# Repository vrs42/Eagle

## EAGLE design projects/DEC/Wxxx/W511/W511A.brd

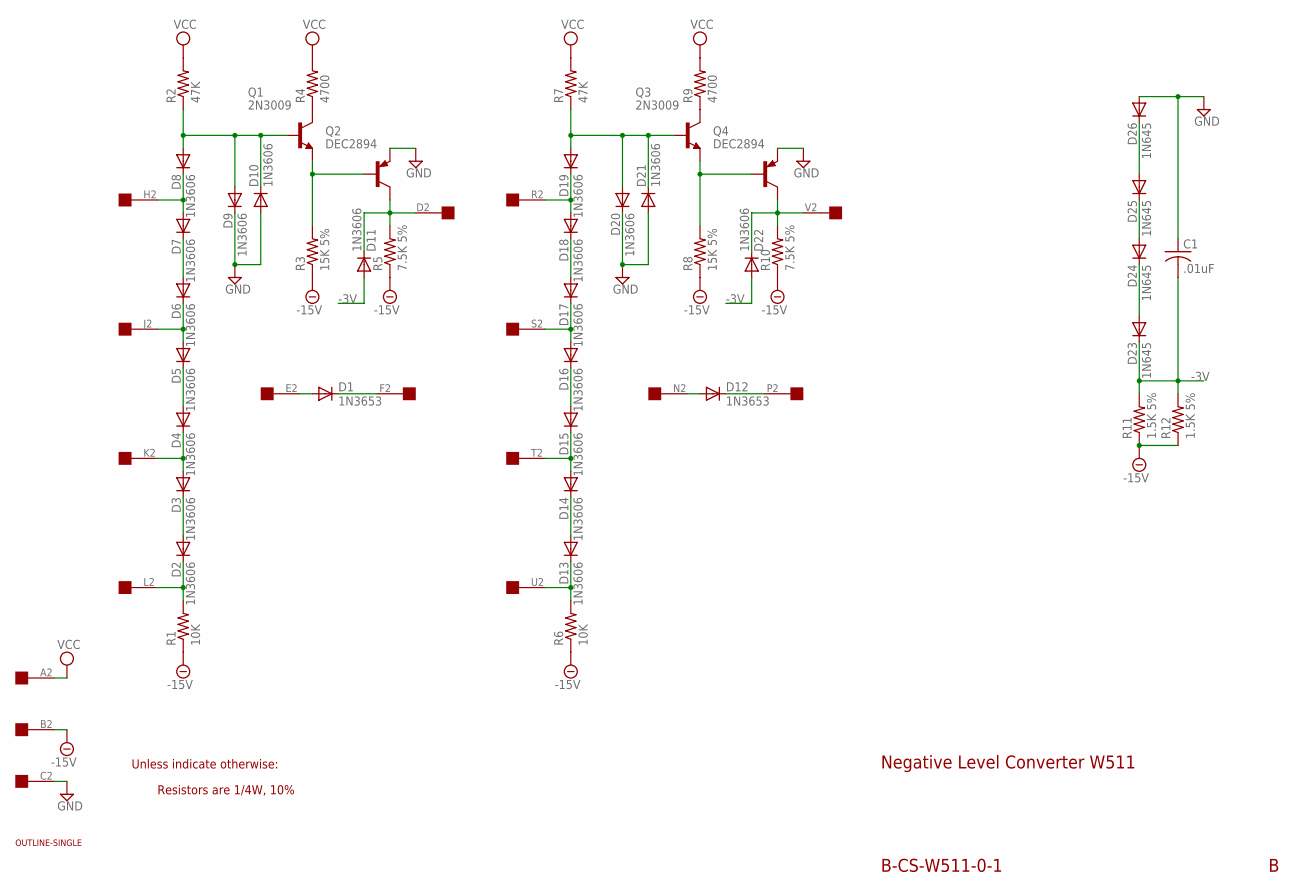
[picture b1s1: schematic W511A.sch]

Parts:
C1: .01uF; C050-025X075
D1, D12: 1N3653; DO35-10
D2, D3, D4, D5, D6, D7, D8, D9, D10, D11, D13, D14, D15, D16, D17, D18, D19, D20, D21, D22: 1N3606; DO35-10
D23, D24, D25, D26: 1N645; DO35-10
EDGE: EDGE-1; EDGE-CON1
Q1, Q3: 2N3009; TO5
Q2, Q4: DEC2894; TO39
R1, R6: 10K; 0207/10
R2, R7: 47K; 0207/10
R3, R8: 15K 5%; 0207/10
R4, R9: 4700; 0207/10
R5, R10: 7.5K 5%; 0207/10
R11, R12: 1.5K 5%; 0207/10
U$1: OUTLINE-SINGLE; SINGLE

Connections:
-3V: C1.2, D11.A, D22.A, D23.C, R11.2, R12.2
-15V: EDGE.B2, R1.1, R3.1, R5.1, R6.1, R8.1, R10.1, R11.1, R12.1
GND: C1.1, D9.C, D10.A, D20.C, D21.A, D26.A, EDGE.C2, Q2.1 (E), Q4.1 (E)
unnamed: D2.A, D3.C
unnamed: D2.C, EDGE.L2, R1.2
unnamed: D3.A, D4.C, EDGE.K2
unnamed: D25.A, D26.C
unnamed: D24.A, D25.C
unnamed: D23.A, D24.C
unnamed: D1.C, EDGE.F2
unnamed: D4.A, D5.C
unnamed: D5.A, D6.C, EDGE.J2
unnamed: D6.A, D7.C
unnamed: D7.A, D8.C, EDGE.H2
unnamed: D8.A, D9.A, D10.C, Q1.2 (B), R2.1
unnamed: Q1.1 (E), Q2.2 (B), R3.2
unnamed: D11.C, EDGE.D2, Q2.3 (C), R5.2
unnamed: Q1.3 (C), R4.1
unnamed: D1.A, EDGE.E2
unnamed: D13.A, D14.C
unnamed: D13.C, EDGE.U2, R6.2
unnamed: D14.A, D15.C, EDGE.T2
unnamed: D15.A, D16.C
unnamed: D16.A, D17.C, EDGE.S2
unnamed: D17.A, D18.C
unnamed: D18.A, D19.C, EDGE.R2
unnamed: D19.A, D20.A, D21.C, Q3.2 (B), R7.1
unnamed: Q3.3 (C), R9.1
unnamed: Q3.1 (E), Q4.2 (B), R8.2
unnamed: D22.C, EDGE.V2, Q4.3 (C), R10.2
unnamed: D12.C, EDGE.P2
unnamed: D12.A, EDGE.N2
VCC: EDGE.A2, R2.2, R4.2, R7.2, R9.2

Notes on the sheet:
Negative Level Converter W511
Resistors are 1/4W, 10%
B-CS-W511-0-1
Unless indicate otherwise:

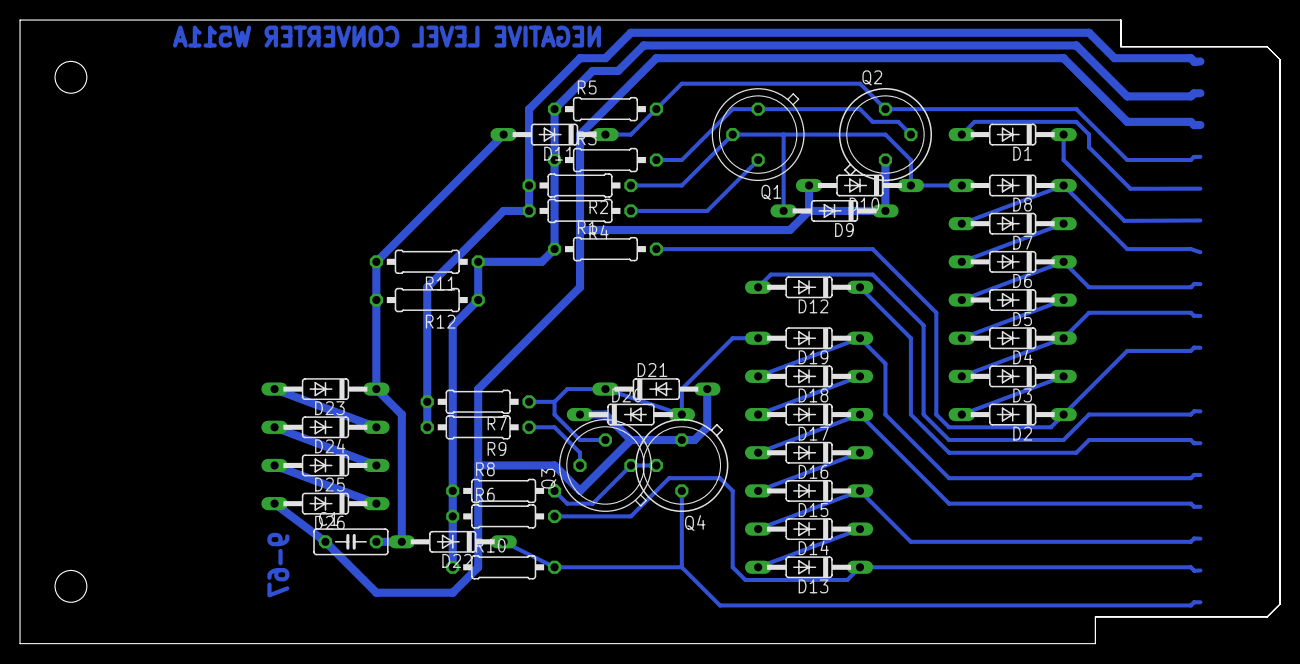
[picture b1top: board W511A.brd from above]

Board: 2 copper layers, 125.7 x 62.2 mm, 45 parts (0 on the bottom side), 33 nets.

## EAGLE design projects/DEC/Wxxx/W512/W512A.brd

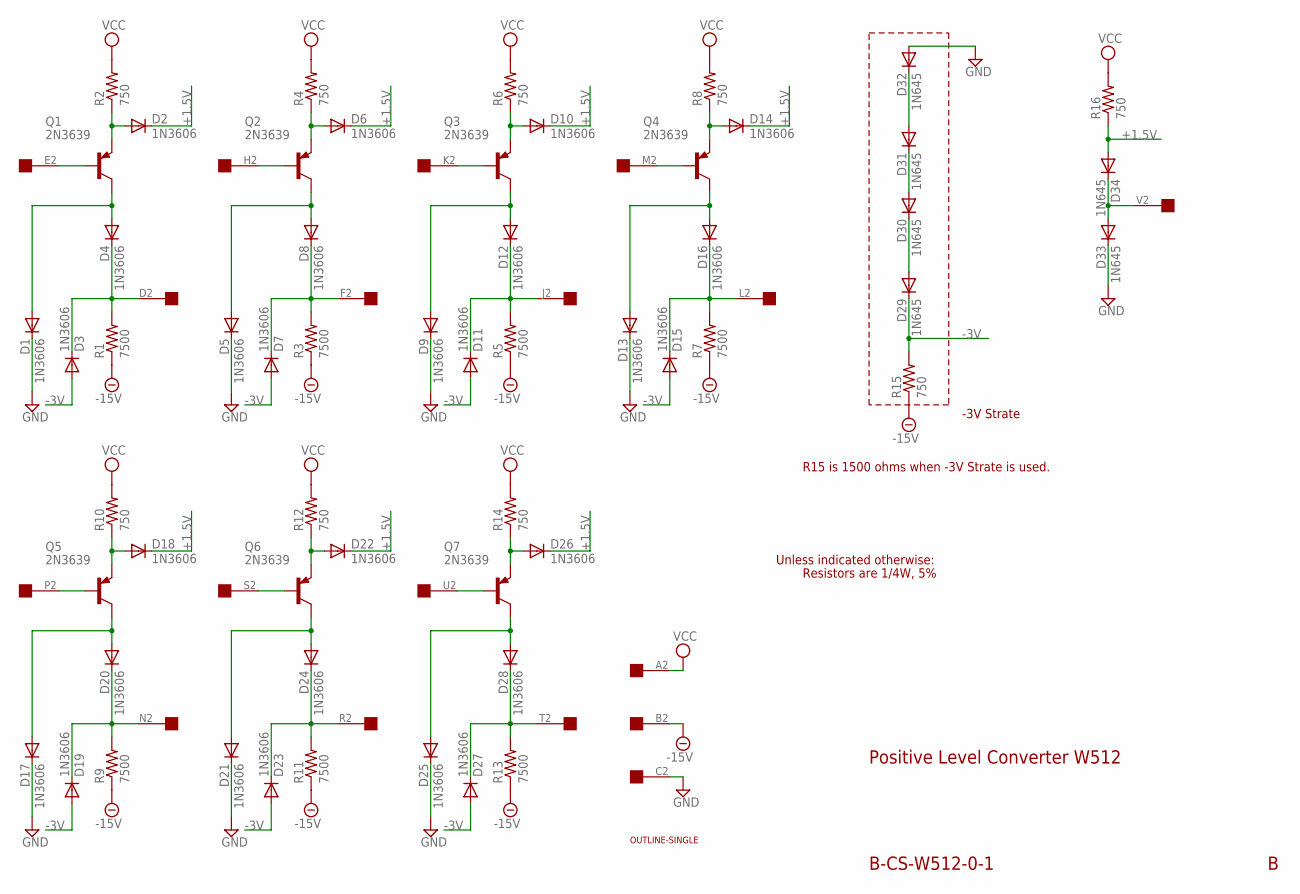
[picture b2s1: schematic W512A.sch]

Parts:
D1, D2, D3, D4, D5, D6, D7, D8, D9, D10, D11, D12, D13, D14, D15, D16, D17, D18, D19, D20, D21, D22, D23, D24, D25, D26, D27, D28: 1N3606; DO35-10
D29, D30, D31, D32, D33, D34: 1N645; DO35-10
EDGE: EDGE-1; EDGE-CON1
Q1, Q2, Q3, Q4, Q5, Q6, Q7: 2N3639; TO39
R1, R3, R5, R7, R9, R11, R13: 7500; 0207/10
R2, R4, R6, R8, R10, R12, R14, R15, R16: 750; 0207/10
U$1: OUTLINE-SINGLE; SINGLE

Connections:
+1.5V: D2.C, D6.C, D10.C, D14.C, D18.C, D22.C, D26.C, D34.A, R16.1
-3V: D3.A, D7.A, D11.A, D15.A, D19.A, D23.A, D27.A, D29.C, R15.2
-15V: EDGE.B2, R1.1, R3.1, R5.1, R7.1, R9.1, R11.1, R13.1, R15.1
GND: D1.C, D5.C, D9.C, D13.C, D17.C, D21.C, D25.C, D32.A, D33.C, EDGE.C2
unnamed: D1.A, D4.A, Q1.3 (C)
unnamed: D3.C, D4.C, EDGE.D2, R1.2
unnamed: EDGE.H2, Q2.2 (B)
unnamed: D31.A, D32.C
unnamed: D30.A, D31.C
unnamed: D29.A, D30.C
unnamed: D2.A, Q1.1 (E), R2.1
unnamed: D6.A, Q2.1 (E), R4.1
unnamed: D5.A, D8.A, Q2.3 (C)
unnamed: D7.C, D8.C, EDGE.F2, R3.2
unnamed: EDGE.K2, Q3.2 (B)
unnamed: D10.A, Q3.1 (E), R6.1
unnamed: EDGE.E2, Q1.2 (B)
unnamed: D9.A, D12.A, Q3.3 (C)
unnamed: D11.C, D12.C, EDGE.J2, R5.2
unnamed: EDGE.M2, Q4.2 (B)
unnamed: D14.A, Q4.1 (E), R8.1
unnamed: D13.A, D16.A, Q4.3 (C)
unnamed: D15.C, D16.C, EDGE.L2, R7.2
unnamed: EDGE.P2, Q5.2 (B)
unnamed: D18.A, Q5.1 (E), R10.1
unnamed: D17.A, D20.A, Q5.3 (C)
unnamed: D19.C, D20.C, EDGE.N2, R9.2
unnamed: EDGE.S2, Q6.2 (B)
unnamed: D22.A, Q6.1 (E), R12.1
unnamed: D21.A, D24.A, Q6.3 (C)
unnamed: D23.C, D24.C, EDGE.R2, R11.2
unnamed: EDGE.U2, Q7.2 (B)
unnamed: D26.A, Q7.1 (E), R14.1
unnamed: D25.A, D28.A, Q7.3 (C)
unnamed: D27.C, D28.C, EDGE.T2, R13.2
unnamed: D33.A, D34.C, EDGE.V2
VCC: EDGE.A2, R2.2, R4.2, R6.2, R8.2, R10.2, R12.2, R14.2, R16.2

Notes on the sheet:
Positive Level Converter W512
Resistors are 1/4W, 5%
B-CS-W512-0-1
Unless indicated otherwise:
-3V Strate
R15 is 1500 ohms when -3V Strate is used.

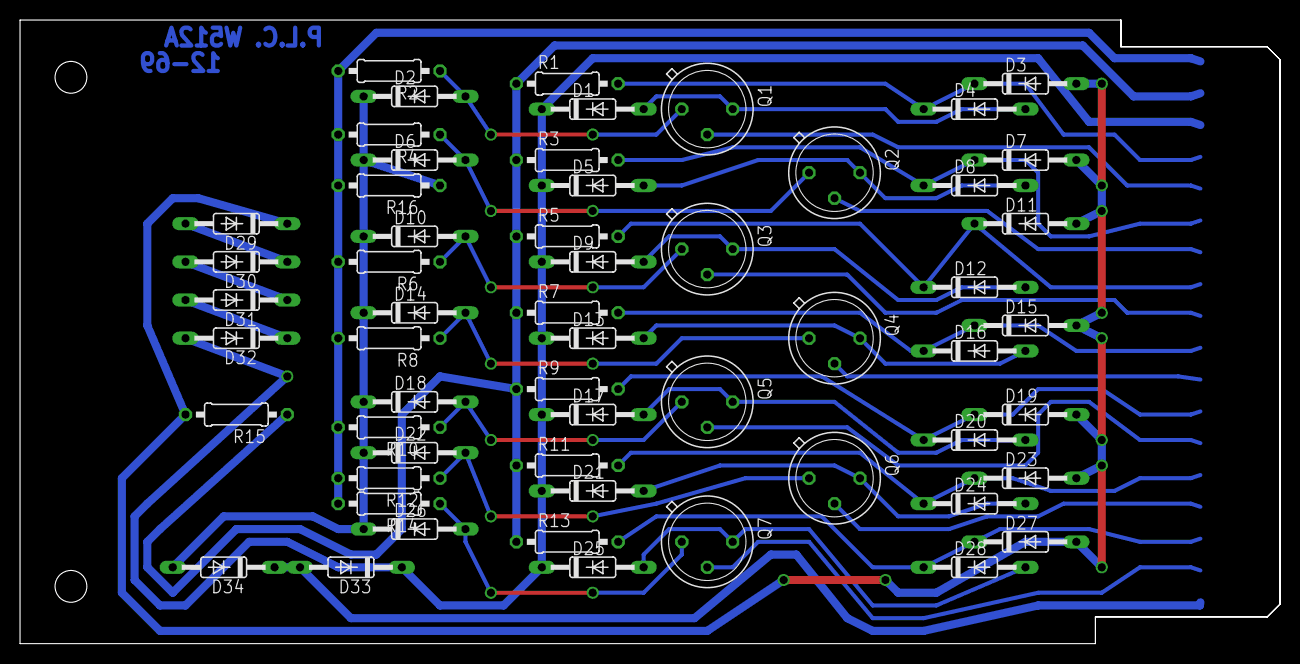
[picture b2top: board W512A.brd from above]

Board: 2 copper layers, 125.7 x 62.2 mm, 59 parts (0 on the bottom side), 37 nets.

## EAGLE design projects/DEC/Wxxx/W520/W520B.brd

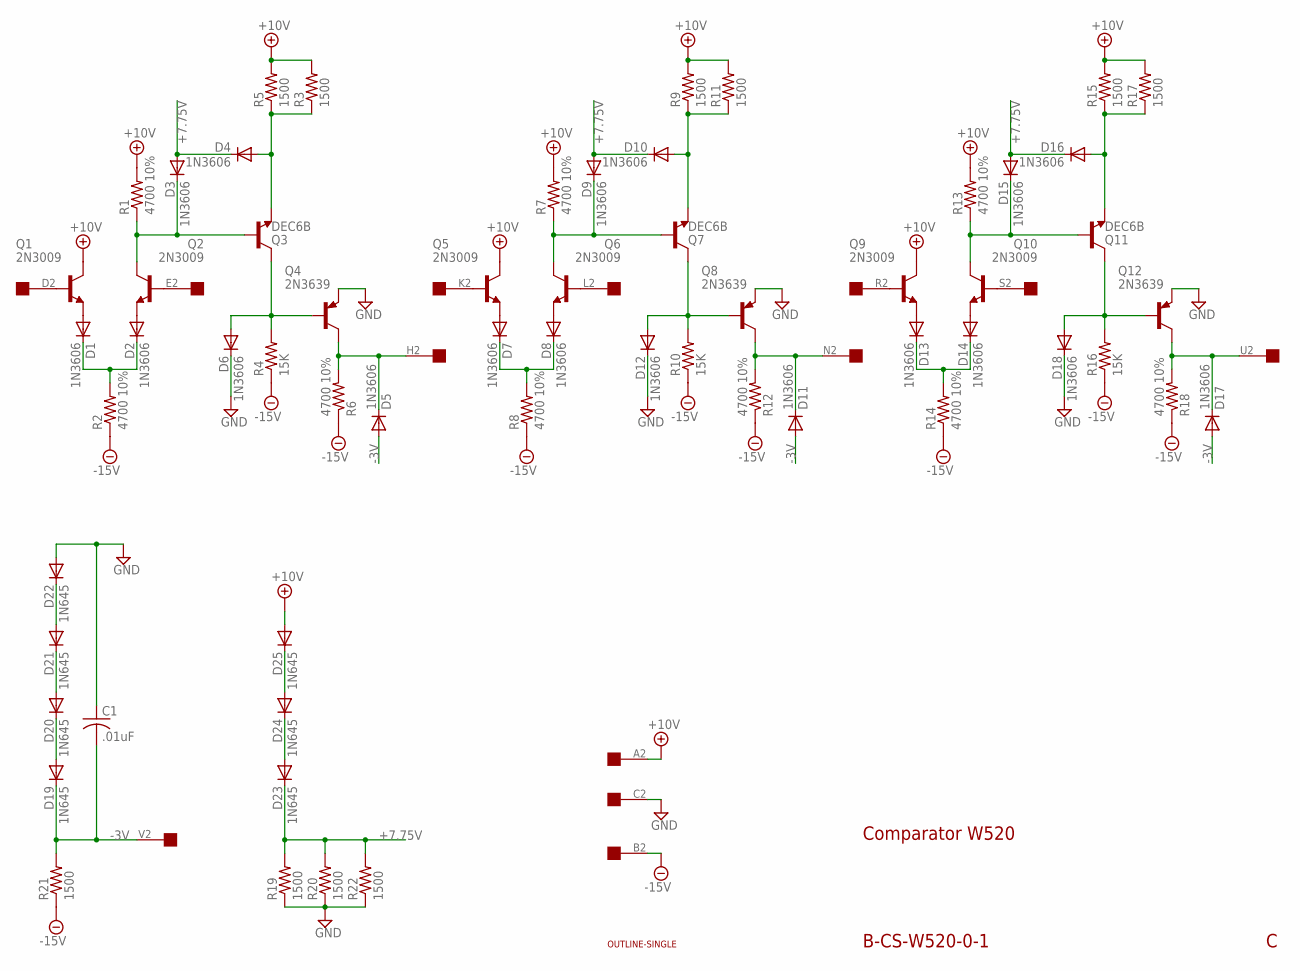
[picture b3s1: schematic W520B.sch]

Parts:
C1: .01uF; C150-054X183
D1, D2, D3, D4, D5, D6, D7, D8, D9, D10, D11, D12, D13, D14, D15, D16, D17, D18: 1N3606; DO35-10
D19, D20, D21, D22, D23, D24, D25: 1N645; DO35-10
Q1, Q2, Q5, Q6, Q9, Q10: 2N3009; TO5
Q3, Q7, Q11: DEC6B; TO5
Q4, Q8, Q12: 2N3639; TO39
R1, R2, R6, R7, R8, R12, R13, R14, R18: 4700 10%; 0207/10
R3, R5, R9, R11, R15, R17, R19, R20, R21, R22: 1500; 0207/10
R4, R10, R16: 15K; 0207/10
U$1: OUTLINE-SINGLE; SINGLE
U$2: EDGE-1; EDGE-CON1

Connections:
+7.75V: D3.A, D4.C, D9.A, D10.C, D15.A, D16.C, D23.C, R19.2, R20.2, R22.2
+10V: D25.A, Q1.3 (C), Q5.3 (C), Q9.3 (C), R1.2, R3.2, R5.2, R7.2, R9.2, R11.2, R13.2, R15.2, R17.2, U$2.A2
-3V: C1.2, D5.A, D11.A, D17.A, D19.C, R21.2, U$2.V2
-15V: R2.1, R4.1, R6.1, R8.1, R10.1, R12.1, R14.1, R16.1, R18.1, R21.1, U$2.B2
GND: C1.1, D6.C, D12.C, D18.C, D22.A, Q4.1 (E), Q8.1 (E), Q12.1 (E), R19.1, R20.1, R22.1, U$2.C2
unnamed: D20.A, D21.C
unnamed: Q1.2 (B), U$2.D2
unnamed: Q2.2 (B), U$2.E2
unnamed: D1.A, Q1.1 (E)
unnamed: D2.A, Q2.1 (E)
unnamed: D1.C, D2.C, R2.2
unnamed: D4.A, Q3.1 (E), R3.1, R5.1
unnamed: D3.C, Q2.3 (C), Q3.2 (B), R1.1
unnamed: D5.C, Q4.3 (C), R6.2, U$2.H2
unnamed: D6.A, Q3.3 (C), Q4.2 (B), R4.2
unnamed: Q5.2 (B), U$2.K2
unnamed: Q6.2 (B), U$2.L2
unnamed: D7.A, Q5.1 (E)
unnamed: D8.A, Q6.1 (E)
unnamed: D7.C, D8.C, R8.2
unnamed: D10.A, Q7.1 (E), R9.1, R11.1
unnamed: D9.C, Q6.3 (C), Q7.2 (B), R7.1
unnamed: D12.A, Q7.3 (C), Q8.2 (B), R10.2
unnamed: D11.C, Q8.3 (C), R12.2, U$2.N2
unnamed: Q9.2 (B), U$2.R2
unnamed: Q10.2 (B), U$2.S2
unnamed: D13.A, Q9.1 (E)
unnamed: D14.A, Q10.1 (E)
unnamed: D13.C, D14.C, R14.2
unnamed: D16.A, Q11.1 (E), R15.1, R17.1
unnamed: D15.C, Q10.3 (C), Q11.2 (B), R13.1
unnamed: D21.A, D22.C
unnamed: D18.A, Q11.3 (C), Q12.2 (B), R16.2
unnamed: D19.A, D20.C
unnamed: D17.C, Q12.3 (C), R18.2, U$2.U2
unnamed: D24.A, D25.C
unnamed: D23.A, D24.C

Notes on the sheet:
Comparator W520
B-CS-W520-0-1

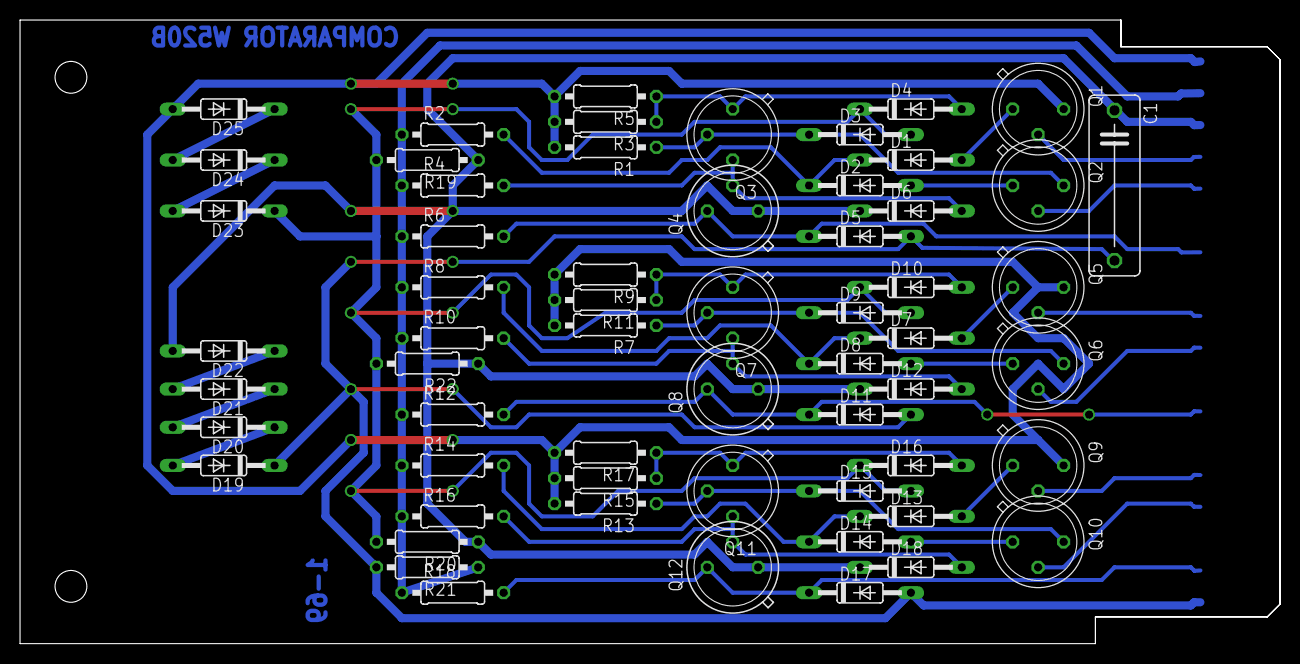
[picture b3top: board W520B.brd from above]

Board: 2 copper layers, 125.7 x 62.2 mm, 62 parts (0 on the bottom side), 37 nets.

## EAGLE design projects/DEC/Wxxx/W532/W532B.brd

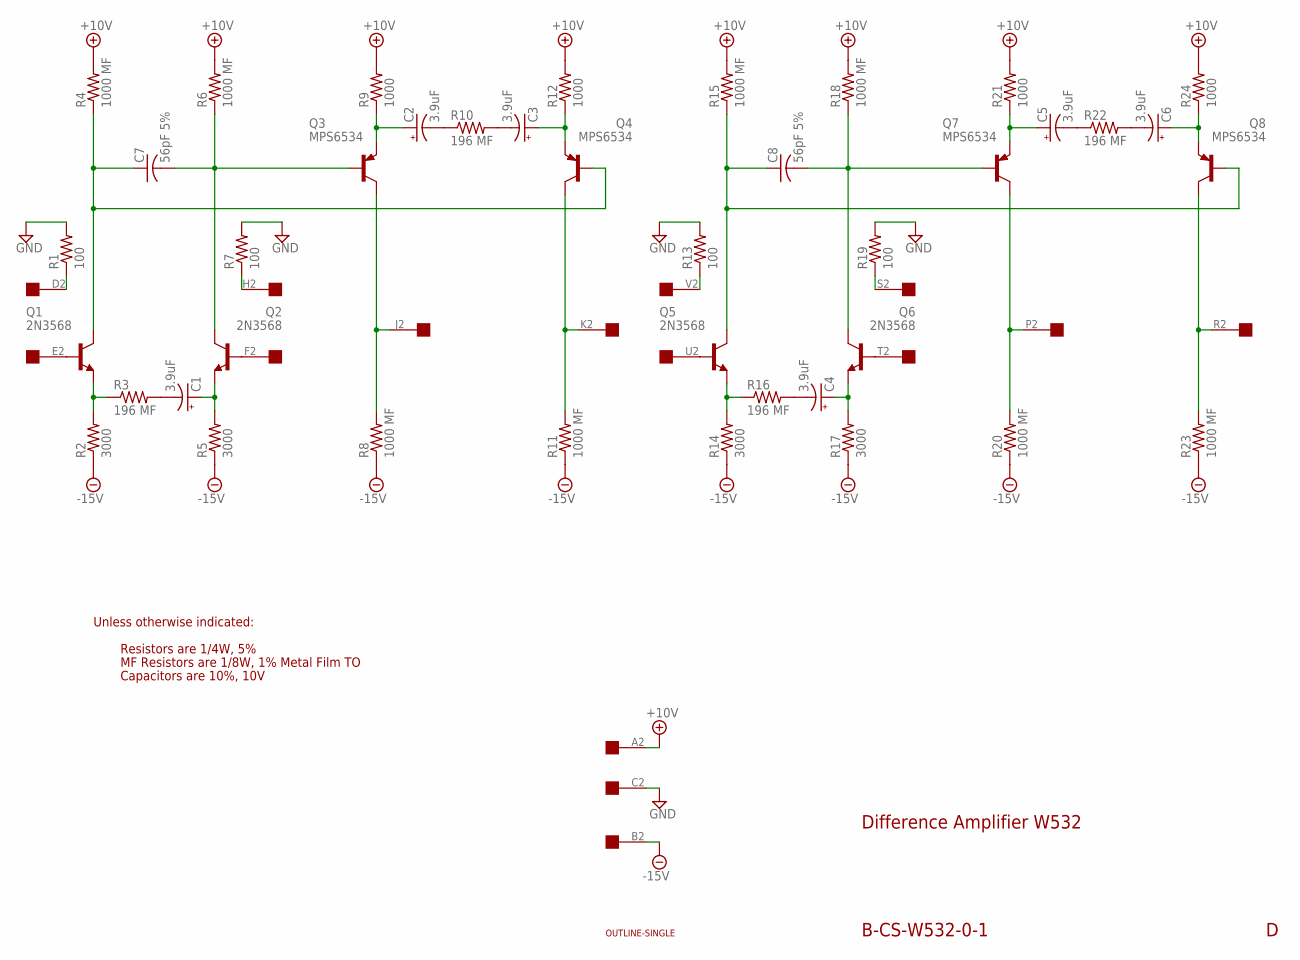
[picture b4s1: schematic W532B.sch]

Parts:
C1, C2, C3, C4, C5, C6: 3.9uF; E15-5
C7, C8: 56pF 5%; C150-054X183
Q1, Q2, Q5, Q6: 2N3568; TO5
Q3, Q4, Q7, Q8: MPS6534; TO39
R1, R7, R13, R19: 100; 0207/10
R2, R5, R14, R17: 3000; 0207/10
R3, R10, R16, R22: 196 MF; 0207/15
R4, R6, R8, R11, R15, R18, R20, R23: 1000 MF; 0207/15
R9, R12, R21, R24: 1000; 0207/10
U$1: OUTLINE-SINGLE; SINGLE
U$2: EDGE-1; EDGE-CON1

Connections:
+10V: R4.2, R6.2, R9.2, R12.2, R15.2, R18.2, R21.2, R24.2, U$2.A2
-15V: R2.1, R5.1, R8.1, R11.1, R14.1, R17.1, R20.1, R23.1, U$2.B2
GND: R1.2, R7.2, R13.2, R19.2, U$2.C2
unnamed: C2.-, R10.1
unnamed: C3.-, R10.2
unnamed: C2.+, Q3.1 (E), R9.1
unnamed: C3.+, Q4.1 (E), R12.1
unnamed: C7.1, Q1.3 (C), Q4.2 (B), R4.1
unnamed: C7.2, Q2.3 (C), Q3.2 (B), R6.1
unnamed: Q3.3 (C), R8.2, U$2.J2
unnamed: Q4.3 (C), R11.2, U$2.K2
unnamed: C1.-, R3.2
unnamed: Q1.2 (B), U$2.E2
unnamed: Q2.2 (B), U$2.F2
unnamed: R1.1, U$2.D2
unnamed: R7.1, U$2.H2
unnamed: Q1.1 (E), R2.2, R3.1
unnamed: C1.+, Q2.1 (E), R5.2
unnamed: C5.-, R22.1
unnamed: C6.-, R22.2
unnamed: C5.+, Q7.1 (E), R21.1
unnamed: C6.+, Q8.1 (E), R24.1
unnamed: C8.2, Q6.3 (C), Q7.2 (B), R18.1
unnamed: C8.1, Q5.3 (C), Q8.2 (B), R15.1
unnamed: Q7.3 (C), R20.2, U$2.P2
unnamed: Q8.3 (C), R23.2, U$2.R2
unnamed: C4.-, R16.2
unnamed: Q5.2 (B), U$2.U2
unnamed: Q6.2 (B), U$2.T2
unnamed: R13.1, U$2.V2
unnamed: R19.1, U$2.S2
unnamed: Q5.1 (E), R14.2, R16.1
unnamed: C4.+, Q6.1 (E), R17.2

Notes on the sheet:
Difference Amplifier W532
B-CS-W532-0-1
Unless otherwise indicated:
Resistors are 1/4W, 5%
MF Resistors are 1/8W, 1% Metal Film TO
Capacitors are 10%, 10V

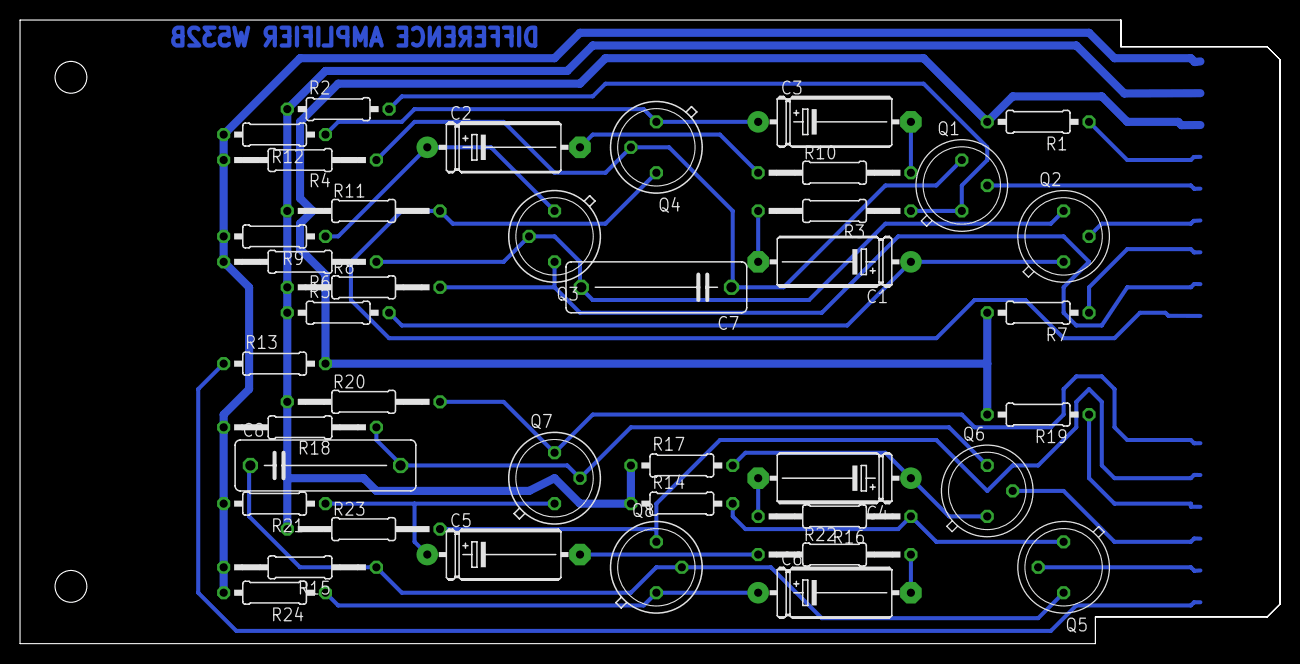
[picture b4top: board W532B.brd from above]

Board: 2 copper layers, 125.7 x 62.2 mm, 42 parts (0 on the bottom side), 33 nets.
